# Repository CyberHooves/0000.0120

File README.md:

# 0000.0120
Indicator boards for 1U enclosures

Small boards for 5, 6, 10 or 12 LED indicators with a maximum height of 36mm for usee in 1U rack mounting enclosures. These are for Kingbright L-93A8CB and L-93A8EB PCB mounting indicators, and attach to a main board using 0.1" pitch right-angled pin headers.

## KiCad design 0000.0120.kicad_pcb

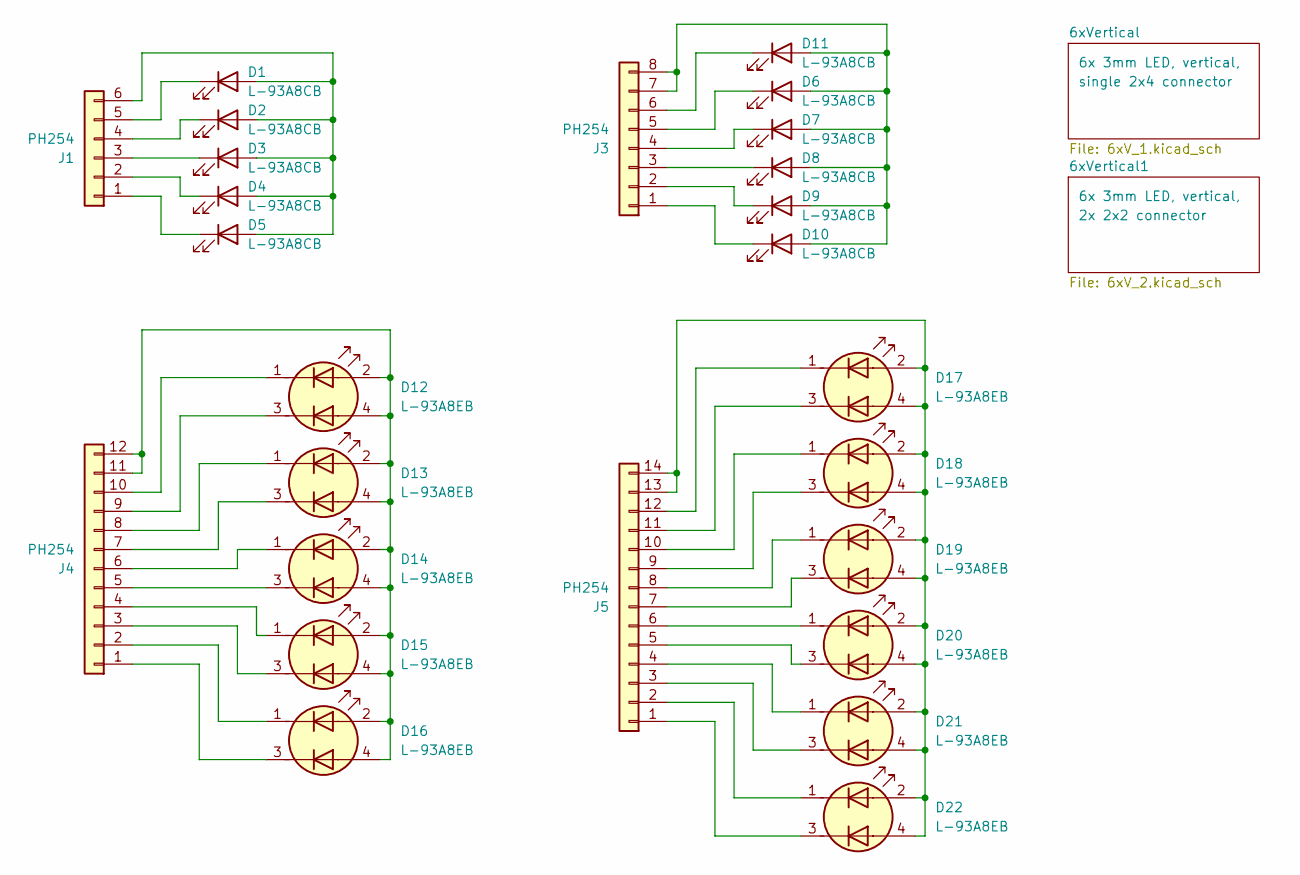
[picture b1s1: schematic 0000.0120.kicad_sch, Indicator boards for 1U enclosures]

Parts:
D1, D2, D3, D4, D5, D6, D7, D8, D9, D10, D11: L-93A8CB; LED_KINGBRIGHT_L-93A8CB
D12, D13, D14, D15, D16, D17, D18, D19, D20, D21, D22: L-93A8EB; LED_KINGBRIGHT_L-93A8EB
J1: PH254; PinHeader_2x03_P2.54mm_Horizontal
J3: PH254; PinHeader_2x04_P2.54mm_Horizontal
J4: PH254; PinHeader_2x06_P2.54mm_Horizontal
J5: PH254; PinHeader_2x07_P2.54mm_Horizontal

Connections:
unnamed: D1.2 (A), D2.2 (A), D3.2 (A), D4.2 (A), D5.2 (A), J1.6
unnamed: D1.1 (K), J1.5
unnamed: D2.1 (K), J1.4
unnamed: D3.1 (K), J1.3
unnamed: D4.1 (K), J1.2
unnamed: D5.1 (K), J1.1
unnamed: D6.1 (K), J3.5
unnamed: D7.1 (K), J3.4
unnamed: D8.1 (K), J3.3
unnamed: D9.1 (K), J3.2
unnamed: D6.2 (A), D7.2 (A), D8.2 (A), D9.2 (A), D10.2 (A), D11.2 (A), J3.7, J3.8
unnamed: D10.1 (K), J3.1
unnamed: D11.1 (K), J3.6
unnamed: D12.2 (A1), D12.4 (A2), D13.2 (A1), D13.4 (A2), D14.2 (A1), D14.4 (A2), D15.2 (A1), D15.4 (A2), D16.2 (A1), D16.4 (A2), J4.11, J4.12
unnamed: D12.1 (K1), J4.10
unnamed: D12.3 (K2), J4.9
unnamed: D13.1 (K1), J4.8
unnamed: D13.3 (K2), J4.7
unnamed: D14.1 (K1), J4.6
unnamed: D14.3 (K2), J4.5
unnamed: D15.1 (K1), J4.4
unnamed: D15.3 (K2), J4.3
unnamed: D16.1 (K1), J4.2
unnamed: D16.3 (K2), J4.1
unnamed: D17.2 (A1), D17.4 (A2), D18.2 (A1), D18.4 (A2), D19.2 (A1), D19.4 (A2), D20.2 (A1), D20.4 (A2), D21.2 (A1), D21.4 (A2), D22.2 (A1), D22.4 (A2), J5.13, J5.14
unnamed: D17.1 (K1), J5.12
unnamed: D17.3 (K2), J5.11
unnamed: D18.1 (K1), J5.10
unnamed: D18.3 (K2), J5.9
unnamed: D19.1 (K1), J5.8
unnamed: D19.3 (K2), J5.7
unnamed: D20.1 (K1), J5.6
unnamed: D20.3 (K2), J5.5
unnamed: D21.1 (K1), J5.4
unnamed: D21.3 (K2), J5.3
unnamed: D22.1 (K1), J5.2
unnamed: D22.3 (K2), J5.1

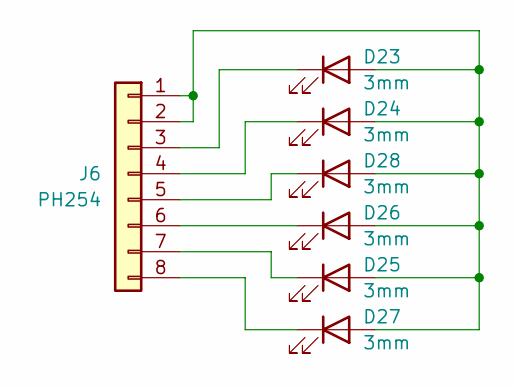
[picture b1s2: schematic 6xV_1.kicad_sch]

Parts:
D23, D24, D25, D26, D27, D28: 3mm; LED_D3.0mm
J6: PH254; PinHeader_2x04_P2.54mm_Horizontal

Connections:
unnamed: D23.2 (A), D24.2 (A), D25.2 (A), D26.2 (A), D27.2 (A), D28.2 (A), J6.1, J6.2
unnamed: D23.1 (K), J6.3
unnamed: D24.1 (K), J6.4
unnamed: D25.1 (K), J6.7
unnamed: D26.1 (K), J6.6
unnamed: D27.1 (K), J6.8
unnamed: D28.1 (K), J6.5

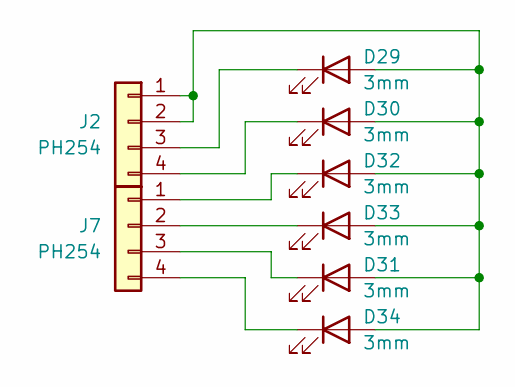
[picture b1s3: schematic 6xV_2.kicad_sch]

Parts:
D29, D30, D31, D32, D33, D34: 3mm; LED_D3.0mm
J2, J7: PH254; PinHeader_2x02_P2.54mm_Horizontal

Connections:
unnamed: D29.2 (A), D30.2 (A), D31.2 (A), D32.2 (A), D33.2 (A), D34.2 (A), J2.1, J2.2
unnamed: D29.1 (K), J2.3
unnamed: D30.1 (K), J2.4
unnamed: D31.1 (K), J7.3
unnamed: D32.1 (K), J7.1
unnamed: D33.1 (K), J7.2
unnamed: D34.1 (K), J7.4

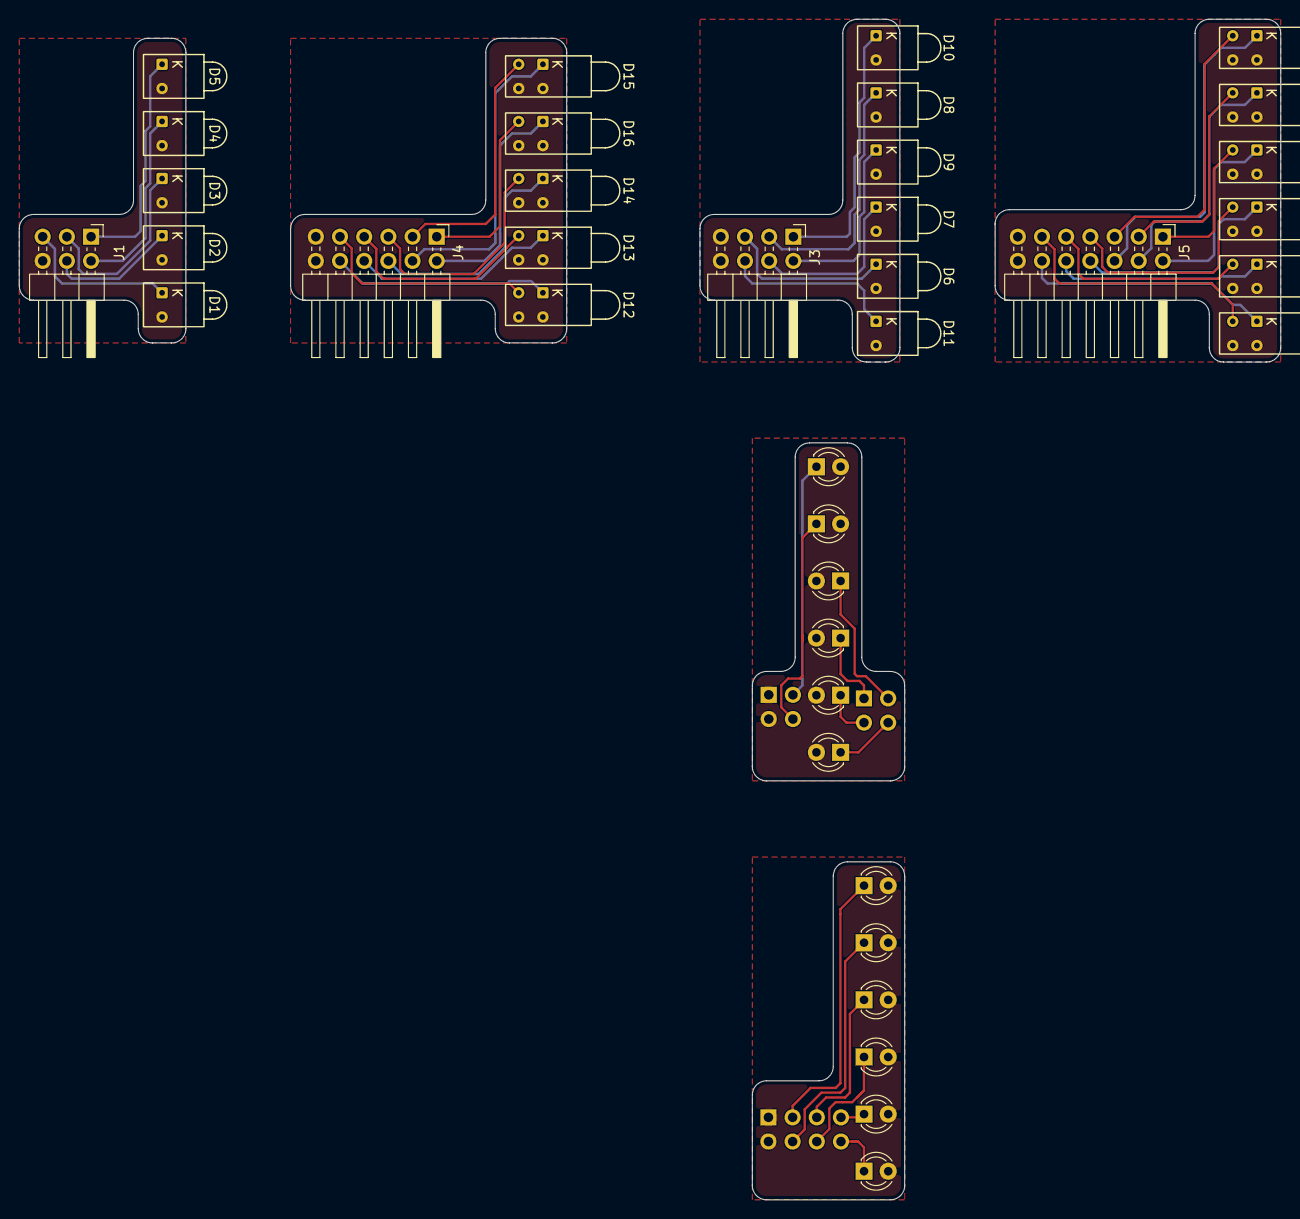
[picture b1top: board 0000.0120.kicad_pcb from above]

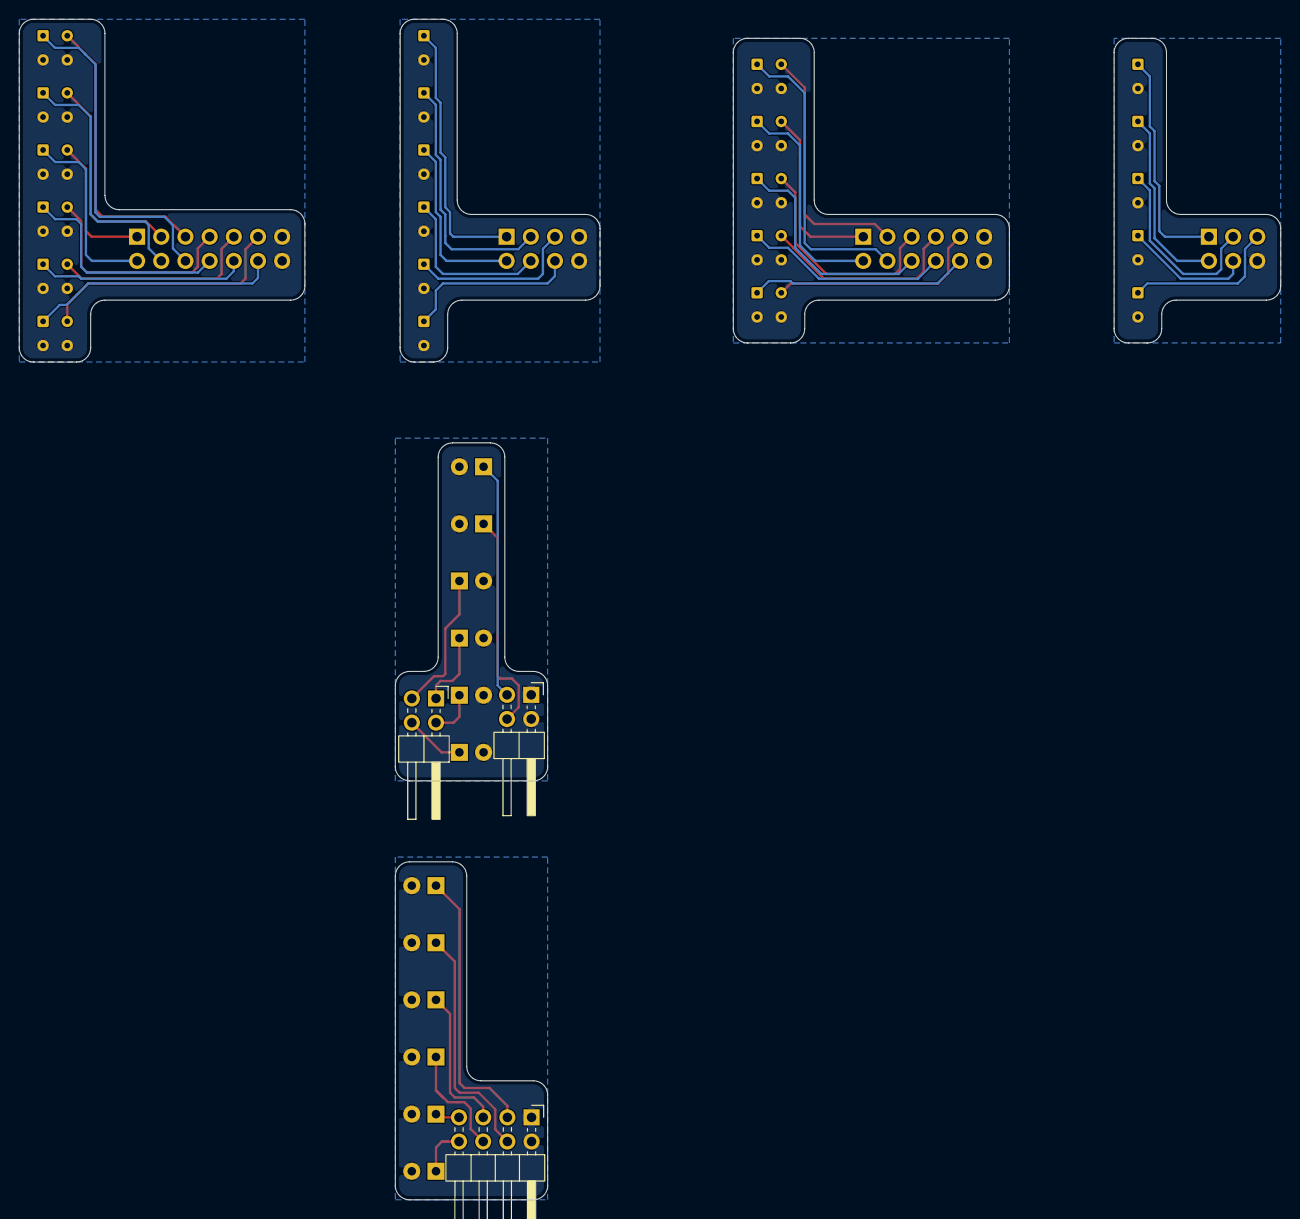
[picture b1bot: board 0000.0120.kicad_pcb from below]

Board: 2 copper layers, 132.5 x 124.0 mm, 41 parts (3 on the bottom side), 51 nets.

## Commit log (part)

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2026-06-13 Files added
2026-06-13 Pinout added
